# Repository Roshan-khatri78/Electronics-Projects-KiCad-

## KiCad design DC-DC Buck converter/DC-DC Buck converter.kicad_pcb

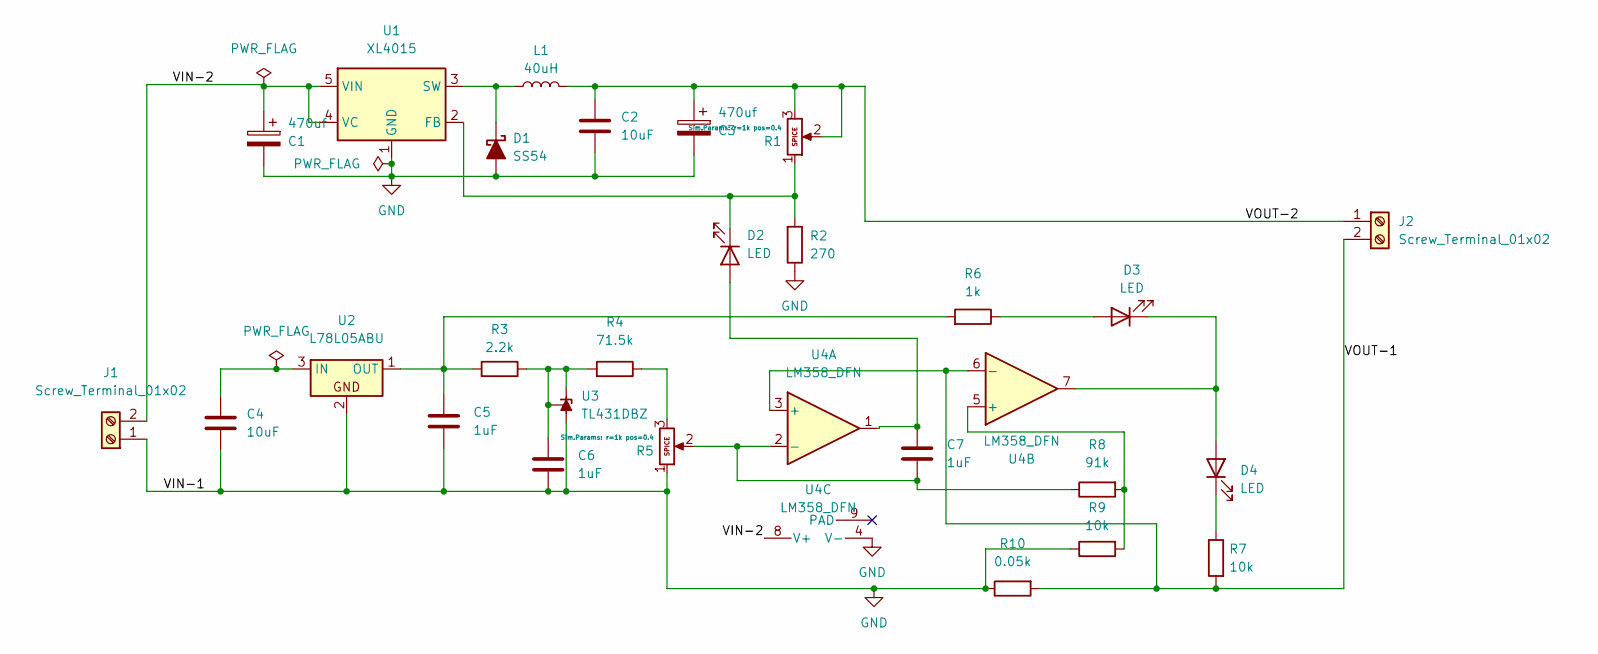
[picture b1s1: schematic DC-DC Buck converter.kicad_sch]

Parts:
C1, C3: 470uf; CP_Elec_10x7.9
C2, C4: 10uF; C_0603_1608Metric
C5, C6, C7: 1uF; C_0603_1608Metric
D1: SS54; D_SMC
D2, D3, D4: LED; LED_0603_1608Metric
J1, J2: Screw_Terminal_01x02; TerminalBlock_Xinya_XY308-2.54-2P_1x02_P2.54mm_Horizontal
L1: 40uH; L_Axial_L5.0mm_D3.6mm_P10.00mm_Horizontal_Murata_BL01RN1A2A2
R1, R5: 10k; Potentiometer_ACP_CA6-H2,5_Horizontal
R2: 270; R_0603_1608Metric
R3: 2.2k; R_0603_1608Metric
R4: 71.5k; R_0603_1608Metric
R6: 1k; R_0603_1608Metric
R7, R9: 10k; R_0603_1608Metric
R8: 91k; R_0603_1608Metric
R10: 0.05k; R_0603_1608Metric
U1: XL4015; TO-263-5_TabPin3
U2: L78L05ABU; SOT-89-3
U3: TL431DBZ; SOT-23
U4: LM358_DFN; SO-8_3.9x4.9mm_P1.27mm

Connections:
/VIN-2: C1.1, J1.2, U1.4 (VC), U1.5 (VIN), U4.8 (V+)
/VOUT-1: J2.2, R7.1, R10.1, U4.3 (+), U4.6 (-)
/VOUT-2: C2.1, C3.1, J2.1, L1.2, R1.2, R1.3
GND: C1.2, C2.2, C3.2, C4.2, C5.2, C6.2, D1.2 (A), J1.1, R2.2, R5.1, R9.2, R10.2, U1.1 (GND), U2.2, U3.3 (A), U4.4 (V-)
unnamed: D1.1 (K), L1.1, U1.3 (SW)
unnamed: C7.1, D2.2 (A), U4.1
unnamed: D2.1 (K), R1.1, R2.1, U1.2 (FB)
unnamed: D3.2 (A), R6.2
unnamed: D3.1 (K), D4.2 (A), U4.7
unnamed: D4.1 (K), R7.2
unnamed: R4.2, R5.3
unnamed: C4.1, U2.3 (IN)
unnamed: C5.1, R3.1, R6.1, U2.1 (OUT)
unnamed: C6.1, R3.2, R4.1, U3.1 (K), U3.2 (REF)
unnamed: C7.2, R5.2, R8.2, U4.2 (-)
unnamed: R8.1, R9.1, U4.5 (+)

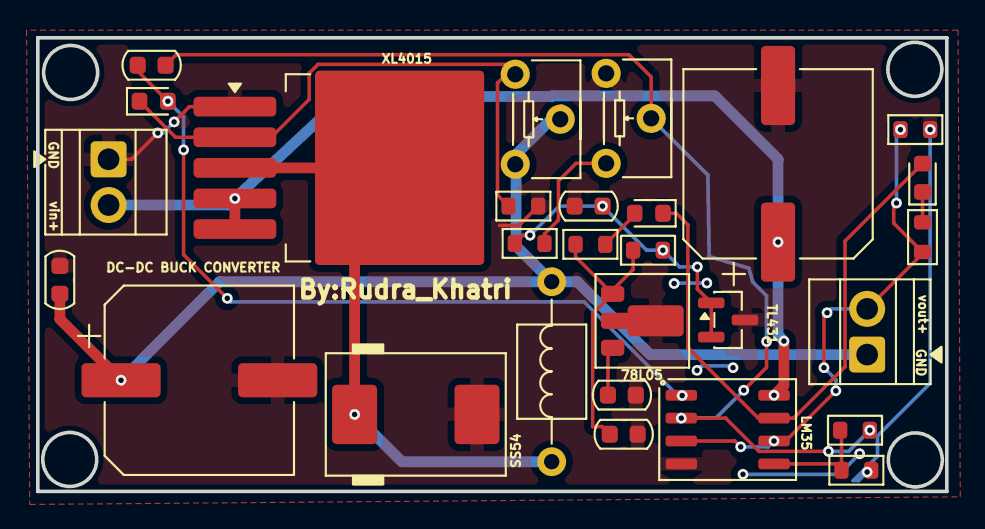
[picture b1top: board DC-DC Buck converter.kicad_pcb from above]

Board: 4 copper layers, 50.5 x 25.2 mm, 28 parts (0 on the bottom side), 16 nets.

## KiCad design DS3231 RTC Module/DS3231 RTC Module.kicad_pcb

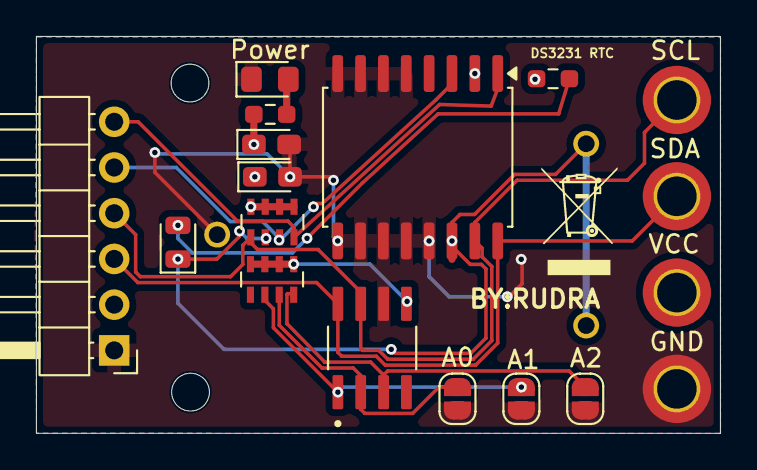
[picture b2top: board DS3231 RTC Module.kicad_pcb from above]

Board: 4 copper layers, 38.0 x 22.0 mm, 19 parts (1 on the bottom side), 12 nets.

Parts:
A0, A1, A2: SolderJumper_2_Open; SolderJumper-2_P1.3mm_Open_RoundedPad1.0x1.5mm
BT1: CR2032W-HE1; BATT_CR2032W-HE1
C1, C2: 0.1uF; CP_EIA-2012-12_Kemet-R_HandSolder
D1: 1N4148; D_0805_2012Metric
H7: SCL; MountingHole_2.2mm_M2_DIN965_Pad_TopBottom
H8: SDA; MountingHole_2.2mm_M2_DIN965_Pad_TopBottom
H9: VCC; MountingHole_2.2mm_M2_DIN965_Pad_TopBottom
H10: GND; MountingHole_2.2mm_M2_DIN965_Pad_TopBottom
J1: Conn_01x06_Pin; PinHeader_1x06_P2.54mm_Horizontal
Power: LED; LED_0805_2012Metric_Pad1.15x1.40mm_HandSolder
R1: 220; R_0603_1608Metric_Pad0.98x0.95mm_HandSolder
R2: 1k; R_0603_1608Metric_Pad0.98x0.95mm_HandSolder
RN1, RN2: 4.7k; R_Array_Concave_4x0603
U1: DS3231M; SOIC-16W_7.5x10.3mm_P1.27mm
U2: SOIC127P600X175-8N

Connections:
/32K: J1.6, RN2.4 (R4.1), U1.1 (32KHZ)
/SCL: H7.1 (1_1), J1.4, RN2.1 (R1.1), U1.15 (SDA), U2.7 (SCL)
/SDA: H8.1 (1_1), J1.3, U1.16 (SCL), U2.8 (SDA)
/SQW: J1.5, RN2.3 (R3.1), U1.3 (~INT/SQW)
GND: A0.1 (A), A1.1 (A), A2.1 (A), BT1.N, C1.2, C2.2, H10.1 (1_1), J1.1, Power.1 (K), U1.5 (GND), U1.6 (GND), U1.7 (GND), U1.8 (GND), U1.9 (GND), U1.10 (GND), U1.11 (GND), U1.12 (GND), U1.13 (GND), U2.6 (WP)
unnamed: D1.2 (A), R1.2
unnamed: BT1.P_1, BT1.P_2, D1.1 (K), RN2.2 (R2.1), U1.14 (VBAT)
unnamed: Power.2 (A), R2.1
unnamed: A0.2 (B), RN1.3 (R3.1), U2.2 (A1)
unnamed: A1.2 (B), RN1.2 (R2.1), U2.1 (A0)
unnamed: A2.2 (B), RN1.4 (R4.1), U2.3 (A2)
VCC: C1.1, C2.1, H9.1 (1_1), J1.2, R1.1, R2.2, RN1.5 (R4.2), RN1.6 (R3.2), RN1.7 (R2.2), RN1.8 (R1.2), RN2.5 (R4.2), RN2.6 (R3.2), RN2.7 (R2.2), RN2.8 (R1.2), U1.2 (VCC), U2.5 (VCC)

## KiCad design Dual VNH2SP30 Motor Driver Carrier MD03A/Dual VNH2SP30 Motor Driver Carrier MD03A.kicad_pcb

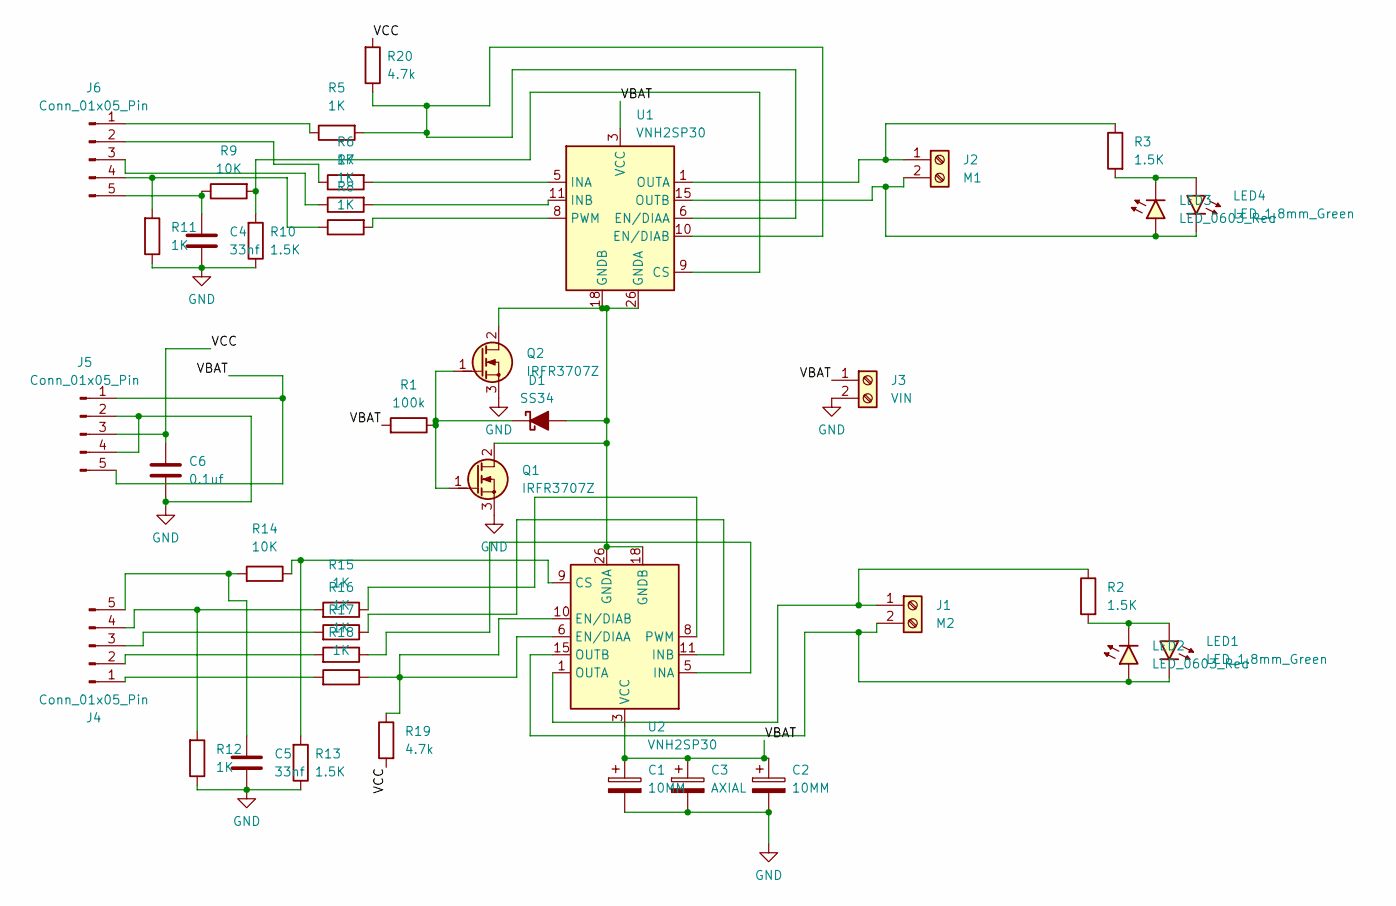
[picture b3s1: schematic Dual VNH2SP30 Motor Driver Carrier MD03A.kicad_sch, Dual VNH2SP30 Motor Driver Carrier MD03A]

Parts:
C1, C2: 10MM; CP_Radial_D4.0mm_P1.50mm
C3: AXIAL; CP_Axial_L10.0mm_D4.5mm_P15.00mm_Horizontal
C4, C5: 33nf; C_0805_2012Metric_Pad1.18x1.45mm_HandSolder
C6: 0.1uf; C_0805_2012Metric_Pad1.18x1.45mm_HandSolder
D1: SS34; D_SMC
J1: M2; TerminalBlock_MaiXu_MX126-5.0-02P_1x02_P5.00mm
J2: M1; TerminalBlock_MaiXu_MX126-5.0-02P_1x02_P5.00mm
J3: VIN; TerminalBlock_MaiXu_MX126-5.0-02P_1x02_P5.00mm
J4, J5, J6: Conn_01x05_Pin; PinHeader_1x05_P2.00mm_Vertical
LED1, LED4: LED_1.8mm_Green; LED_0805_2012Metric_Pad1.15x1.40mm_HandSolder
LED2, LED3: LED_0603_Red; LED_0603_1608Metric
Q1, Q2: IRFR3707Z; TO-252-2
R1: 100k; R_0805_2012Metric_Pad1.20x1.40mm_HandSolder
R2, R3, R10, R13: 1.5K; R_0805_2012Metric_Pad1.20x1.40mm_HandSolder
R5, R6, R7, R8, R11, R12, R15, R16, R17, R18: 1K; R_0805_2012Metric_Pad1.20x1.40mm_HandSolder
R9, R14: 10K; R_0805_2012Metric_Pad1.20x1.40mm_HandSolder
R19, R20: 4.7k; R_0805_2012Metric_Pad1.20x1.40mm_HandSolder
U1, U2: VNH2SP30; ST_MultiPowerSO-30

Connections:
/VBAT: C1.1, C2.1, C3.1, J3.1, J5.1, J5.5, R1.1, U1.3 (VCC), U1.13 (VCC), U1.23 (VCC), U1.31 (VCC), U2.3 (VCC), U2.13 (VCC), U2.23 (VCC), U2.31 (VCC); also elsewhere on the board
/VCC: C6.1, J5.3, R19.1, R20.1
GND: C1.2, C2.2, C3.2, C4.2, C5.2, C6.2, J3.2, J5.2, J5.4, Q1.3 (S), Q2.3 (S), R10.2, R11.2, R12.2, R13.2; also elsewhere on the board
unnamed: D1.2 (A), Q1.2 (D), Q2.2 (D), U1.18 (GNDB), U1.19 (GNDB), U1.20 (GNDB), U1.26 (GNDA), U1.27 (GNDA), U1.28 (GNDA), U2.18 (GNDB), U2.19 (GNDB), U2.20 (GNDB), U2.26 (GNDA), U2.27 (GNDA), U2.28 (GNDA)
unnamed: D1.1 (K), Q1.1 (G), Q2.1 (G), R1.2
unnamed: J1.1, R2.2, U2.1 (OUTA), U2.25 (OUTA), U2.30 (OUTA), U2.33 (OUTA)
unnamed: J1.2, LED1.1 (K), LED2.2 (A), U2.15 (OUTB), U2.16 (OUTB), U2.21 (OUTB), U2.32 (OUTB)
unnamed: J2.1, R3.2, U1.1 (OUTA), U1.25 (OUTA), U1.30 (OUTA), U1.33 (OUTA)
unnamed: J2.2, LED3.2 (A), LED4.1 (K), U1.15 (OUTB), U1.16 (OUTB), U1.21 (OUTB), U1.32 (OUTB)
unnamed 9: J6.1, R5.2; also elsewhere on the board
unnamed 10: J6.2, R6.2; also elsewhere on the board
unnamed 11: J6.3, R7.2; also elsewhere on the board
unnamed 12: J6.4, R8.2, R11.1; also elsewhere on the board
unnamed 13: C4.1, J6.5, R9.2; also elsewhere on the board
unnamed 14: C5.1, J4.5, R14.1; also elsewhere on the board
unnamed 15: J4.4, R12.1, R15.1; also elsewhere on the board
unnamed 16: J4.3, R16.1; also elsewhere on the board
unnamed 17: J4.2, R17.1; also elsewhere on the board
unnamed 18: J4.1, R18.1; also elsewhere on the board
unnamed: LED1.2 (A), LED2.1 (K), R2.1
unnamed: LED3.1 (K), LED4.2 (A), R3.1
unnamed: R9.1, R10.1, U1.9 (CS)
unnamed: R5.1, R20.2, U1.6 (EN/DIAA), U1.10 (EN/DIAB)
unnamed: R6.1, U1.5 (INA)
unnamed: R7.1, U1.11 (INB)
unnamed: R8.1, U1.8 (PWM)
unnamed: R13.1, R14.2, U2.9 (CS)
unnamed: R18.2, R19.2, U2.6 (EN/DIAA), U2.10 (EN/DIAB)
unnamed: R17.2, U2.5 (INA)
unnamed: R16.2, U2.11 (INB)
unnamed: R15.2, U2.8 (PWM)

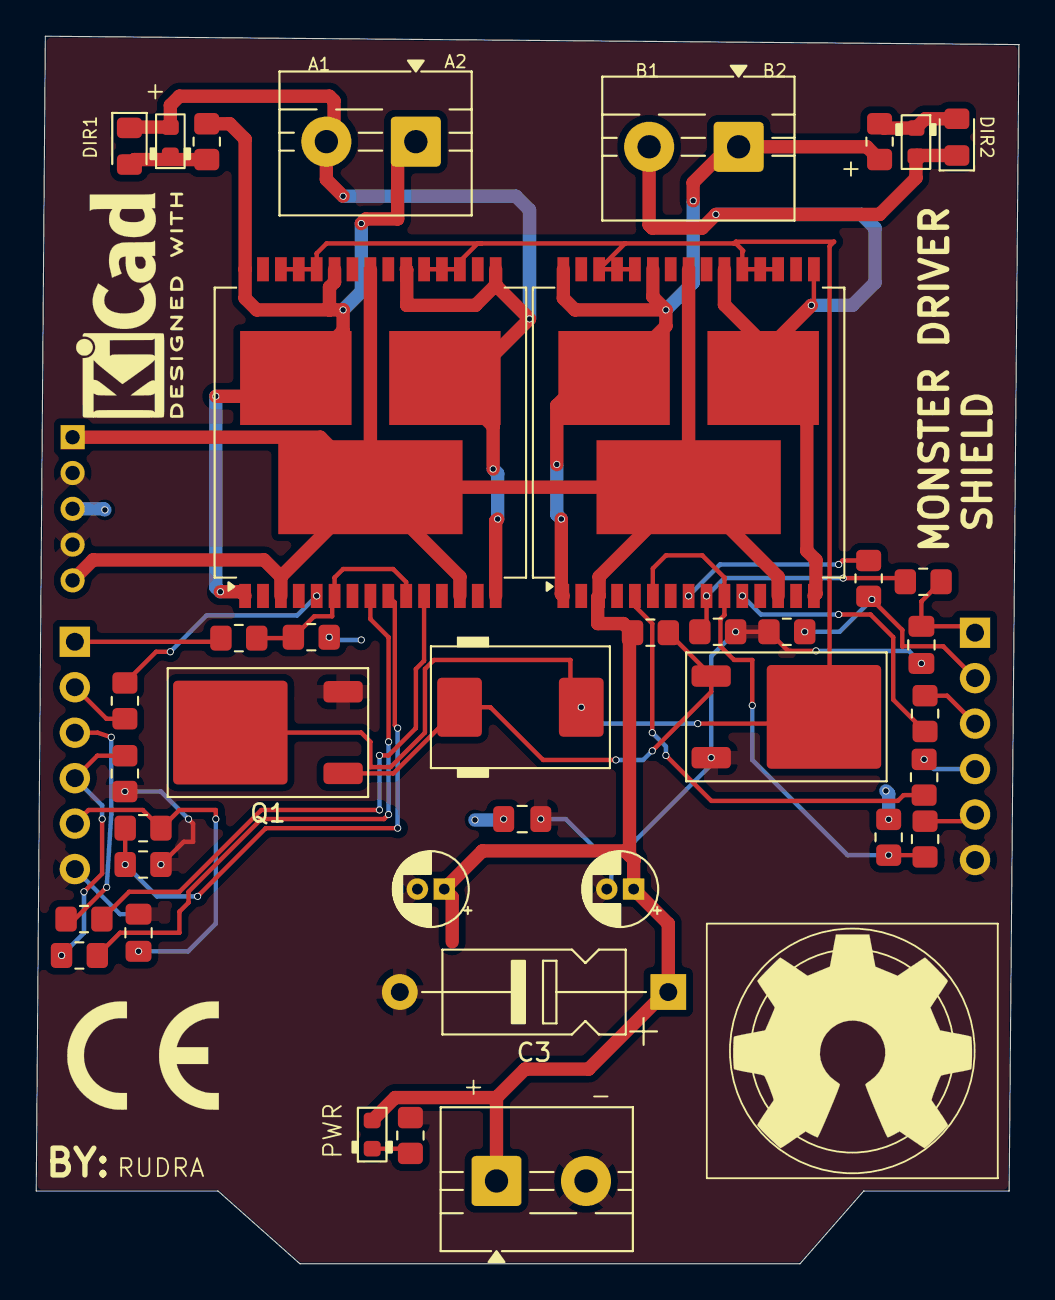
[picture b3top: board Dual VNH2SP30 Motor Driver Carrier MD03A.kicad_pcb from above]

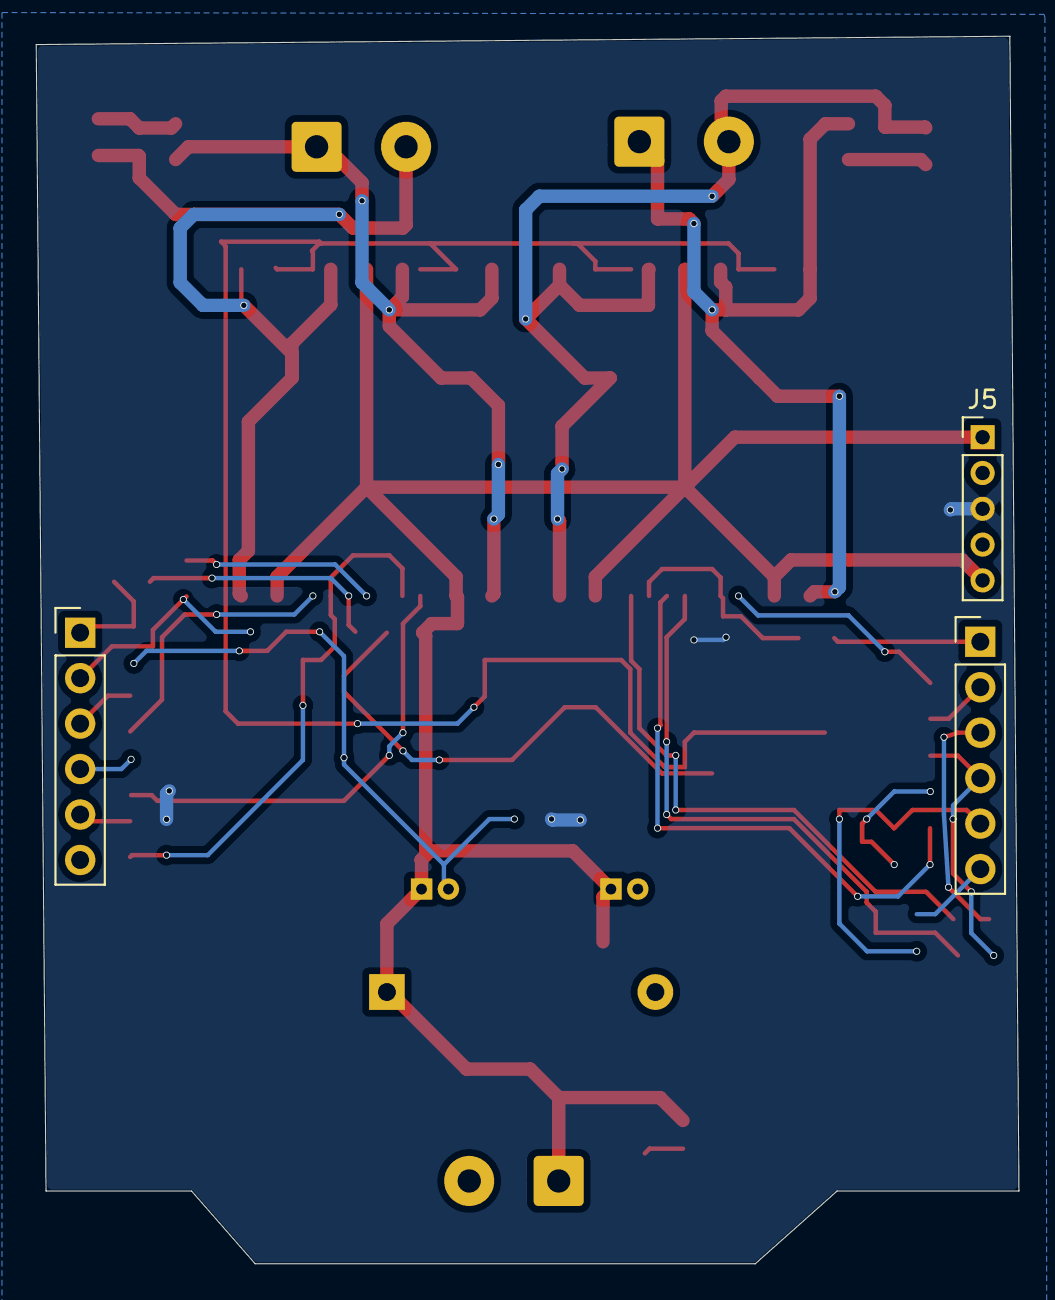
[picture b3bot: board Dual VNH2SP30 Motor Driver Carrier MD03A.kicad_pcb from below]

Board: 4 copper layers, 54.9 x 68.6 mm, 42 parts (3 on the bottom side), 32 nets.

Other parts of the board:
J7, J8: Conn_01x06_Pin; PinHeader_1x06_P2.54mm_Vertical
LED5: LED_0603_Red; LED_0603_1608Metric
R4: 1.5K; R_0805_2012Metric_Pad1.20x1.40mm_HandSolder

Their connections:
/VBAT: LED5.2 (A); also elsewhere on the board
GND: J7.6, J8.6, R4.2; also elsewhere on the board
unnamed 9: J7.1; also elsewhere on the board
unnamed 10: J7.2; also elsewhere on the board
unnamed 11: J7.3; also elsewhere on the board
unnamed 12: J7.4; also elsewhere on the board
unnamed 13: J7.5; also elsewhere on the board
unnamed 14: J8.1; also elsewhere on the board
unnamed 15: J8.2; also elsewhere on the board
unnamed 16: J8.3; also elsewhere on the board
unnamed 17: J8.4; also elsewhere on the board
unnamed 18: J8.5; also elsewhere on the board
unnamed: LED5.1 (K), R4.1

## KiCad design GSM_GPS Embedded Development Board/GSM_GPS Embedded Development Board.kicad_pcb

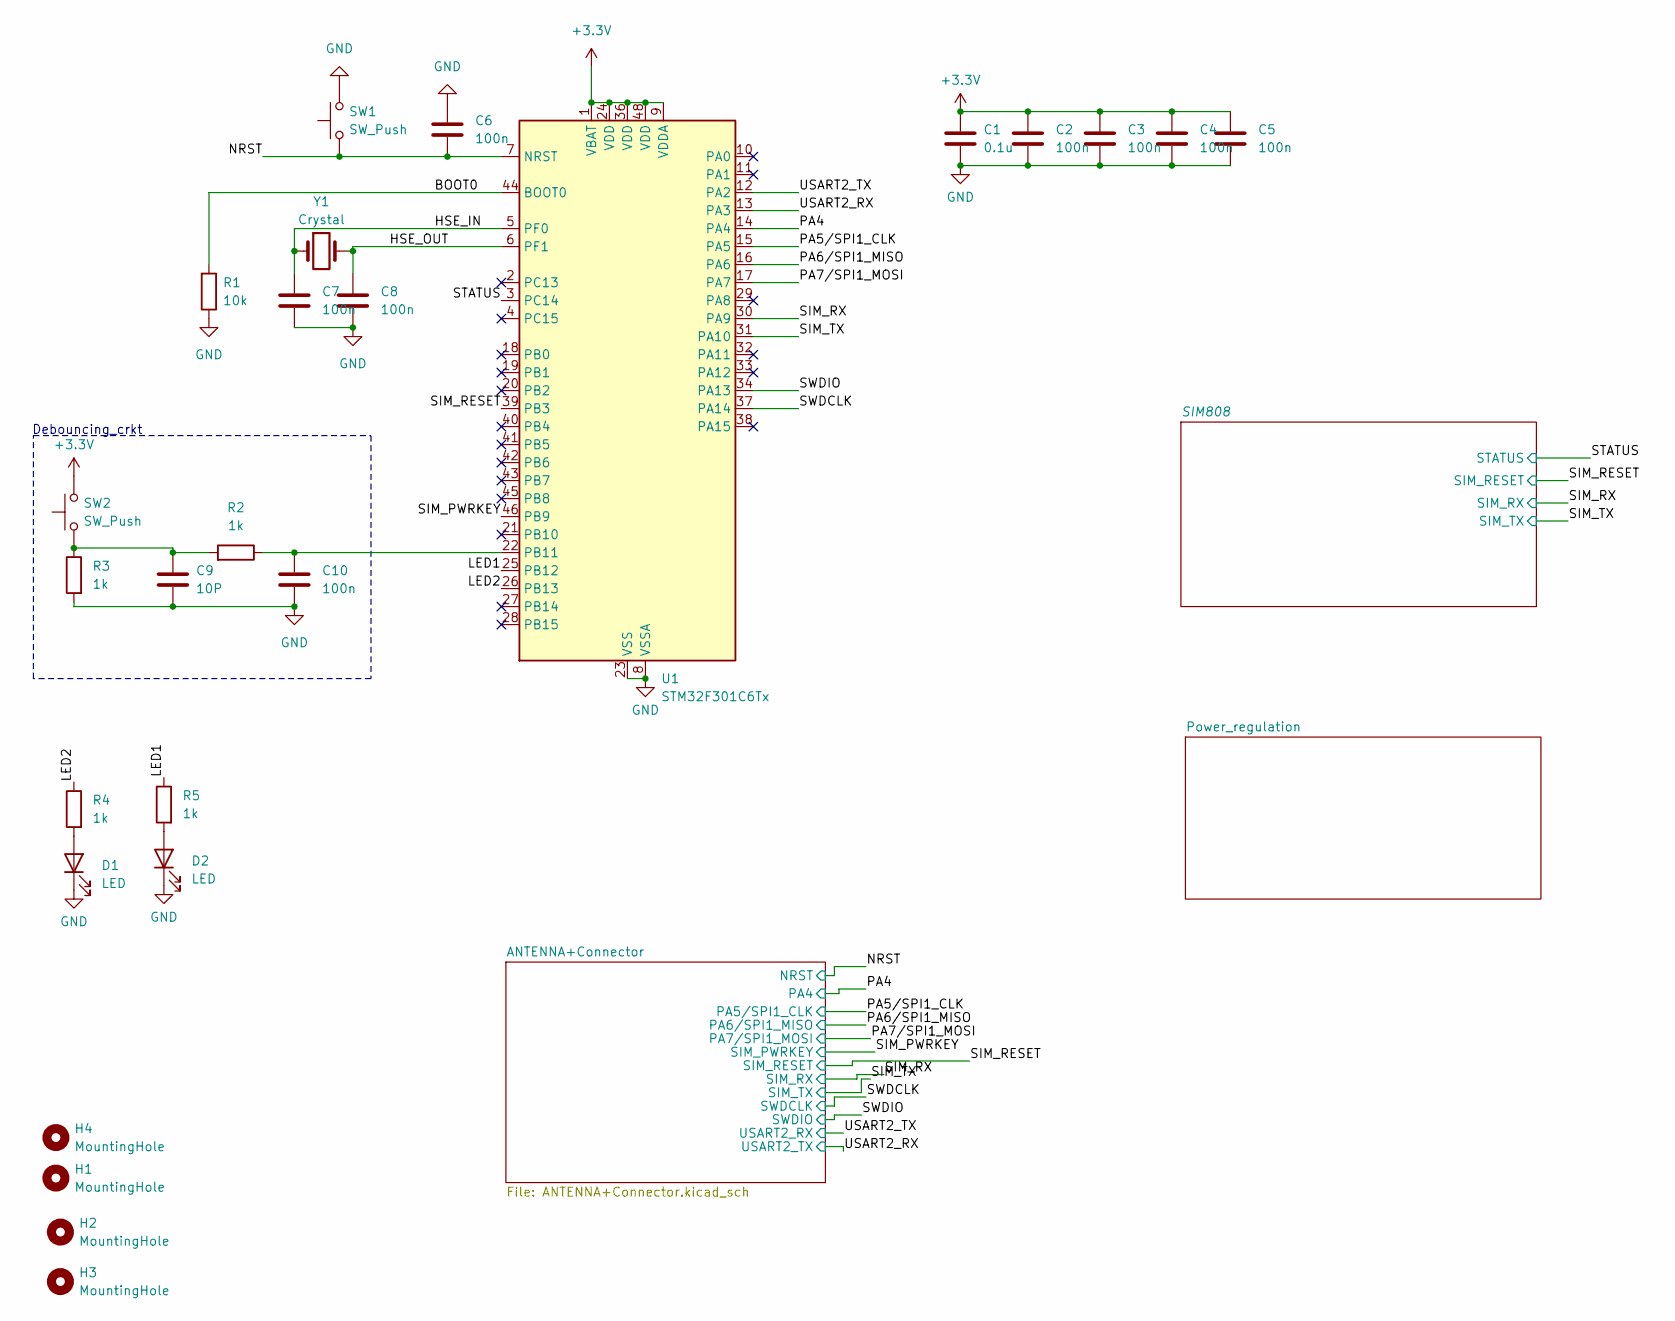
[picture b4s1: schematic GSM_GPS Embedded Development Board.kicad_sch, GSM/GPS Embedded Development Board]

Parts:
C1: 0.1u; CP_EIA-2012-12_Kemet-R_HandSolder
C2, C3, C4, C5, C6, C7, C8, C10: 100n; C_0201_0603Metric_Pad0.64x0.40mm_HandSolder
C9: 10P; C_0201_0603Metric_Pad0.64x0.40mm_HandSolder
D1, D2: LED; LED_0402_1005Metric_Pad0.77x0.64mm_HandSolder
H1, H2, H3, H4: MountingHole; MountingHole_2.1mm
R1: 10k; R_0805_2012Metric_Pad1.20x1.40mm_HandSolder
R2, R3, R4, R5: 1k; R_0805_2012Metric_Pad1.20x1.40mm_HandSolder
SW1, SW2: SW_Push; SW_PUSH_6mm
U1: STM32F301C6Tx; LQFP-48_7x7mm_P0.5mm
Y1: Crystal; Crystal_HC18-U_Vertical

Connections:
+3.3V: C1.1, C2.1, C3.1, C4.1, C5.1, SW2.2, U1.1 (VBAT), U1.9 (VDDA), U1.24 (VDD), U1.36 (VDD), U1.48 (VDD); also elsewhere on the board
/BOOT0: R1.1, U1.44 (BOOT0)
/HSE_IN: C7.1, U1.5 (PF0), Y1.1
/HSE_OUT: C8.1, U1.6 (PF1), Y1.2
/LED1: R5.2, U1.25 (PB12)
/LED2: R4.2, U1.26 (PB13)
/NRST: C6.2, SW1.1, U1.7 (NRST); also elsewhere on the board
/PA4: U1.14 (PA4); also elsewhere on the board
/PA5/SPI1_CLK: U1.15 (PA5); also elsewhere on the board
/PA6/SPI1_MISO: U1.16 (PA6); also elsewhere on the board
/PA7/SPI1_MOSI: U1.17 (PA7); also elsewhere on the board
/SIM_PWRKEY: U1.46 (PB9); also elsewhere on the board
/SIM_RESET: U1.39 (PB3); also elsewhere on the board
/SIM_RX: U1.30 (PA9); also elsewhere on the board
/SIM_TX: U1.31 (PA10); also elsewhere on the board
/STATUS: U1.3 (PC14); also elsewhere on the board
/SWDCLK: U1.37 (PA14); also elsewhere on the board
/SWDIO: U1.34 (PA13); also elsewhere on the board
/USART2_RX: U1.13 (PA3); also elsewhere on the board
/USART2_TX: U1.12 (PA2); also elsewhere on the board
GND: C1.2, C2.2, C3.2, C4.2, C5.2, C6.1, C7.2, C8.2, C9.2, C10.2, D1.1 (K), D2.1 (K), R1.2, R3.1, SW1.2, U1.8 (VSSA), U1.23 (VSS), U1.35 (VSS), U1.47 (VSS); also elsewhere on the board
unnamed: C9.1, R2.1, R3.2, SW2.1
unnamed: D1.2 (A), R4.1
unnamed: D2.2 (A), R5.1
unnamed: C10.1, R2.2, U1.22 (PB11)

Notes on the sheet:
Debouncing_crkt

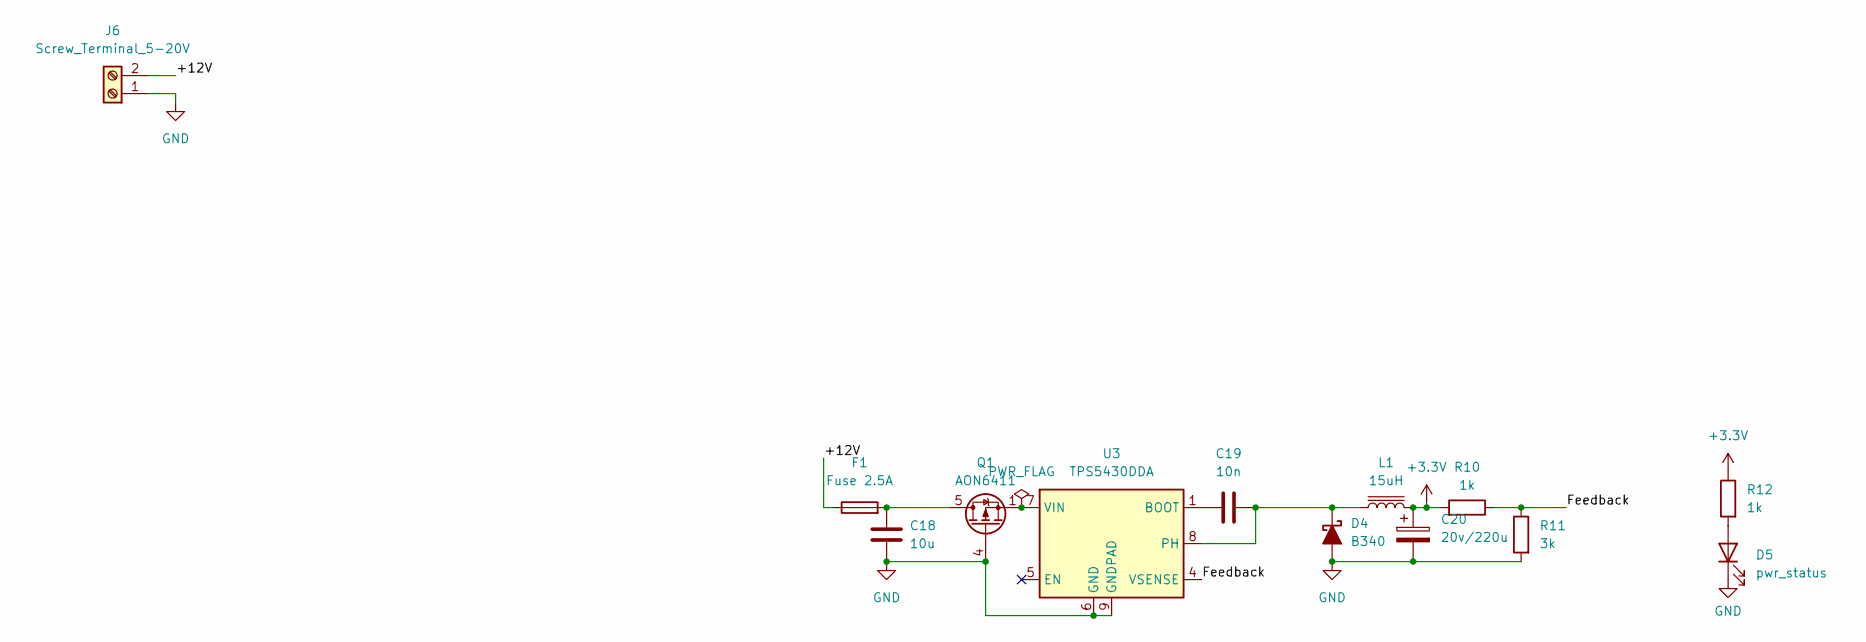
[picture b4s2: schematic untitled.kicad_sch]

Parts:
C18: 10u; C_0201_0603Metric_Pad0.64x0.40mm_HandSolder
C19: 10n; C_0201_0603Metric_Pad0.64x0.40mm_HandSolder
C20: 20v/220u; CP_Elec_3x5.4
D4: B340; D_2010_5025Metric_TVS
D5: pwr_status; LED_0402_1005Metric_Pad0.77x0.64mm_HandSolder
F1: Fuse 2.5A; Fuse_0402_1005Metric_Pad0.77x0.64mm_HandSolder
J6: Screw_Terminal_5-20V; TerminalBlock_MetzConnect_Type059_RT06302HBWC_1x02_P3.50mm_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
L1: 15uH; L_2010_5025Metric_Pad1.52x2.65mm_HandSolder
Q1: AON6411; AO_DFN-8-1EP_5.55x5.2mm_P1.27mm_EP4.12x4.6mm
R10, R12: 1k; R_0805_2012Metric_Pad1.20x1.40mm_HandSolder
R11: 3k; R_0805_2012Metric_Pad1.20x1.40mm_HandSolder
U3: TPS5430DDA; TI_SO-PowerPAD-8_ThermalVias

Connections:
+3.3V: C20.1, L1.2, R10.1, R12.2; also elsewhere on the board
/Power_regulation/+12V: F1.1, J6.2
/Power_regulation/Feedback: R10.2, R11.2, U3.4 (VSENSE)
GND: C18.2, C20.2, D4.2 (A), D5.1 (K), J6.1, Q1.4 (G), R11.1, U3.6 (GND), U3.9 (GNDPAD); also elsewhere on the board
unnamed: C19.2, D4.1 (K), L1.1, U3.8 (PH)
unnamed: D5.2 (A), R12.1
unnamed: C18.1, F1.2, Q1.5 (D)
unnamed: C19.1, U3.1 (BOOT)
unnamed: Q1.1 (S), Q1.2 (S), Q1.3 (S), U3.7 (VIN)

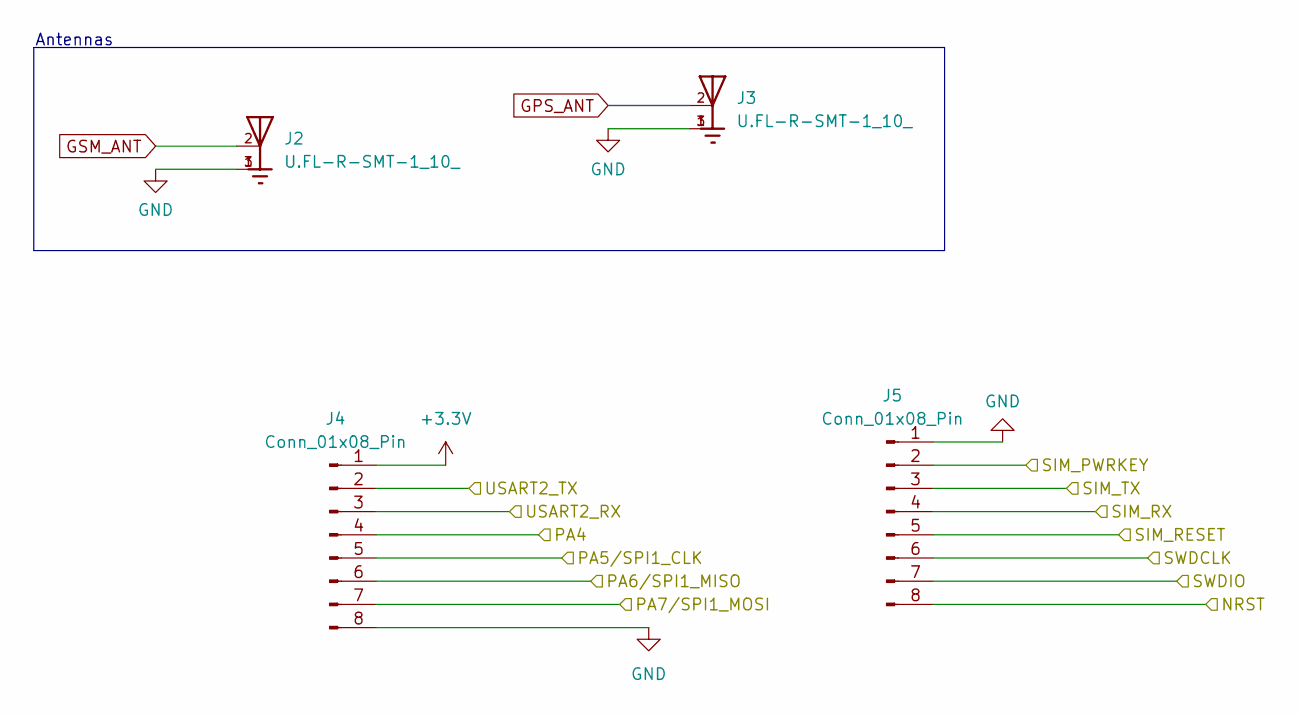
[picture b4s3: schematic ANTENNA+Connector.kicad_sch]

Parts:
J2, J3: U.FL-R-SMT-1_10_; HRS_U.FL-R-SMT-1_10_
J4, J5: Conn_01x08_Pin; JST_EH_B8B-EH-A_1x08_P2.50mm_Vertical

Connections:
+3.3V: J4.1; also elsewhere on the board
/NRST: J5.8; also elsewhere on the board
/PA4: J4.4; also elsewhere on the board
/PA5/SPI1_CLK: J4.5; also elsewhere on the board
/PA6/SPI1_MISO: J4.6; also elsewhere on the board
/PA7/SPI1_MOSI: J4.7; also elsewhere on the board
/SIM_PWRKEY: J5.2; also elsewhere on the board
/SIM_RESET: J5.5; also elsewhere on the board
/SIM_RX: J5.4; also elsewhere on the board
/SIM_TX: J5.3; also elsewhere on the board
/SWDCLK: J5.6; also elsewhere on the board
/SWDIO: J5.7; also elsewhere on the board
/USART2_RX: J4.2; also elsewhere on the board
/USART2_TX: J4.3; also elsewhere on the board
GND: J2.1, J2.3, J3.1, J3.3, J4.8, J5.1; also elsewhere on the board
GPS_ANT: J3.2; also elsewhere on the board
GSM_ANT: J2.2; also elsewhere on the board

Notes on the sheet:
Antennas

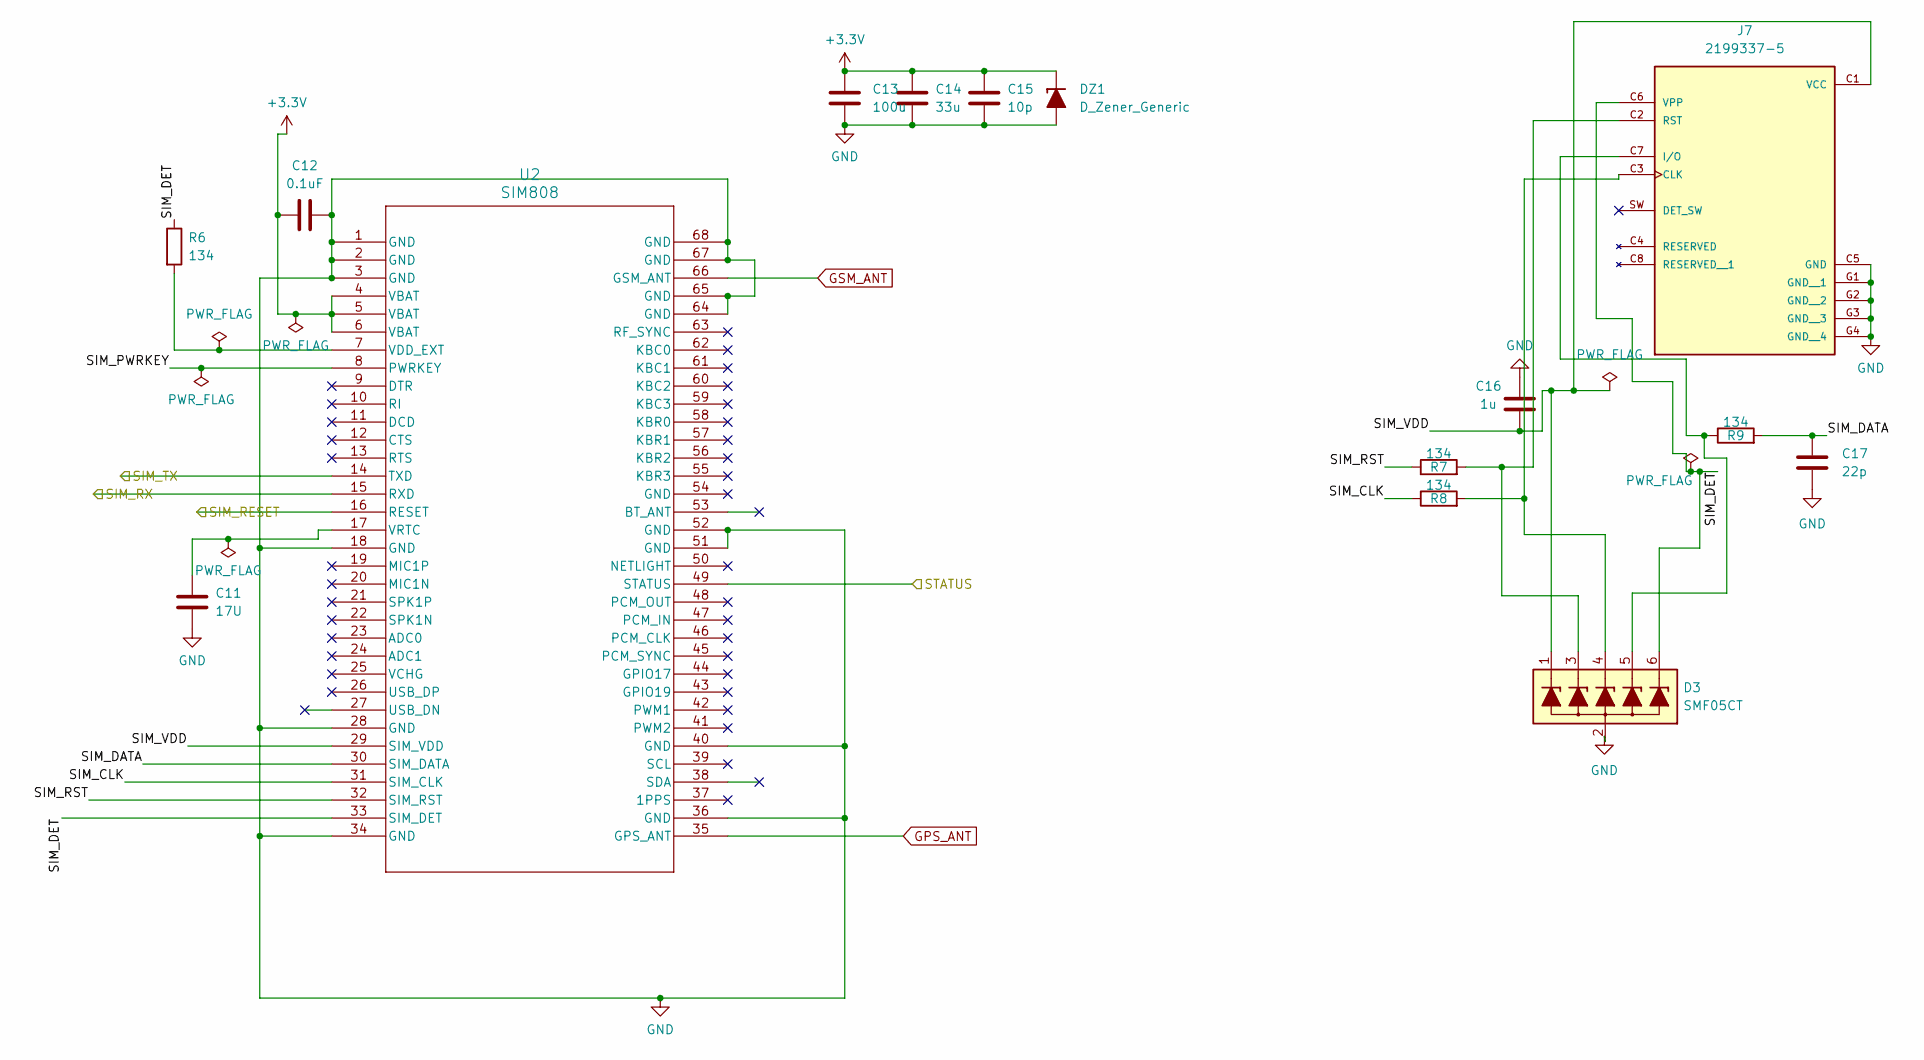
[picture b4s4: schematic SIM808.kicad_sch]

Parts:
C11: 17U; C_0201_0603Metric_Pad0.64x0.40mm_HandSolder
C12: 0.1uF; CP_EIA-2012-12_Kemet-R_HandSolder
C13: 100u; CP_EIA-2012-12_Kemet-R_HandSolder
C14: 33u; C_0201_0603Metric_Pad0.64x0.40mm_HandSolder
C15: 10p; C_0201_0603Metric_Pad0.64x0.40mm_HandSolder
C16: 1u; C_0201_0603Metric_Pad0.64x0.40mm_HandSolder
C17: 22p; C_0201_0603Metric_Pad0.64x0.40mm_HandSolder
D3: SMF05CT; SOT-363_SC-70-6
DZ1: D_Zener_Generic; D_0805_2012Metric_Pad1.15x1.40mm_HandSolder
J7: 2199337-5; TE_2199337-5; PARTREV A2
R6, R7, R8, R9: 134; R_0805_2012Metric_Pad1.20x1.40mm_HandSolder
U2: SIM808; SIM808_SMM

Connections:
+3.3V: C12.1, C13.1, C14.1, C15.1, DZ1.1 (K), U2.4 (VBAT), U2.5 (VBAT), U2.6 (VBAT); also elsewhere on the board
/SIM808/SIM_CLK: R8.1, U2.31 (SIM_CLK)
/SIM808/SIM_DATA: C17.1, R9.2, U2.30 (SIM_DATA)
/SIM808/SIM_DET: D3.6 (L5), J7.C6 (VPP), R6.1, U2.33 (SIM_DET)
/SIM808/SIM_PWRKEY: U2.8 (PWRKEY)
/SIM808/SIM_RST: R7.1, U2.32 (SIM_RST)
/SIM808/SIM_VDD: C16.2, D3.1 (L1), J7.C1 (VCC), U2.29 (SIM_VDD)
/SIM_RESET: U2.16 (RESET); also elsewhere on the board
/SIM_RX: U2.15 (RXD); also elsewhere on the board
/SIM_TX: U2.14 (TXD); also elsewhere on the board
/STATUS: U2.49 (STATUS); also elsewhere on the board
GND: C11.2, C12.2, C13.2, C14.2, C15.2, C16.1, C17.2, D3.2 (VN), DZ1.2 (A), J7.C5 (GND), J7.G1 (GND__1), J7.G2 (GND__2), J7.G3 (GND__3), J7.G4 (GND__4), U2.1 (GND), U2.2 (GND), U2.3 (GND), U2.18 (GND), U2.28 (GND), U2.34 (GND), U2.36 (GND), U2.40 (GND), U2.51 (GND), U2.52 (GND), U2.64 (GND), U2.65 (GND), U2.67 (GND), U2.68 (GND); also elsewhere on the board
GPS_ANT: U2.35 (GPS_ANT); also elsewhere on the board
GSM_ANT: U2.66 (GSM_ANT); also elsewhere on the board
unnamed: D3.3 (L2), J7.C2 (RST), R7.2
unnamed: D3.4 (L3), J7.C3 (CLK), R8.2
unnamed: D3.5 (L4), J7.C7 (I/O), R9.1
unnamed: R6.2, U2.7 (VDD_EXT)
unnamed: C11.1, U2.17 (VRTC)

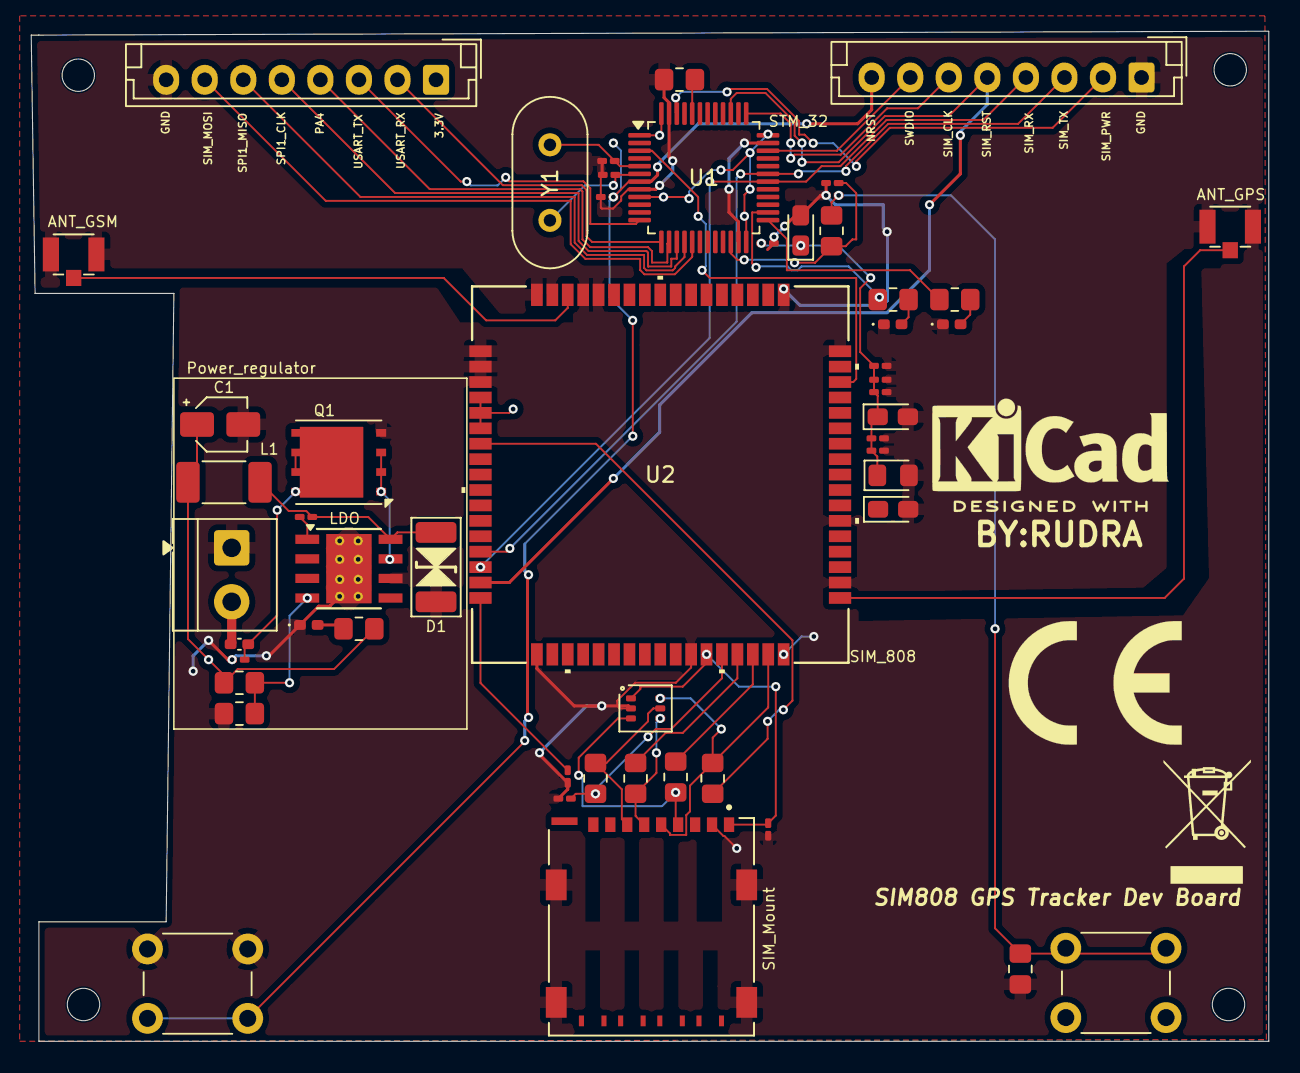
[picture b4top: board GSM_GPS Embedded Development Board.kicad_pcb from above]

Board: 4 copper layers, 80.2 x 65.5 mm, 57 parts (0 on the bottom side), 44 nets.
